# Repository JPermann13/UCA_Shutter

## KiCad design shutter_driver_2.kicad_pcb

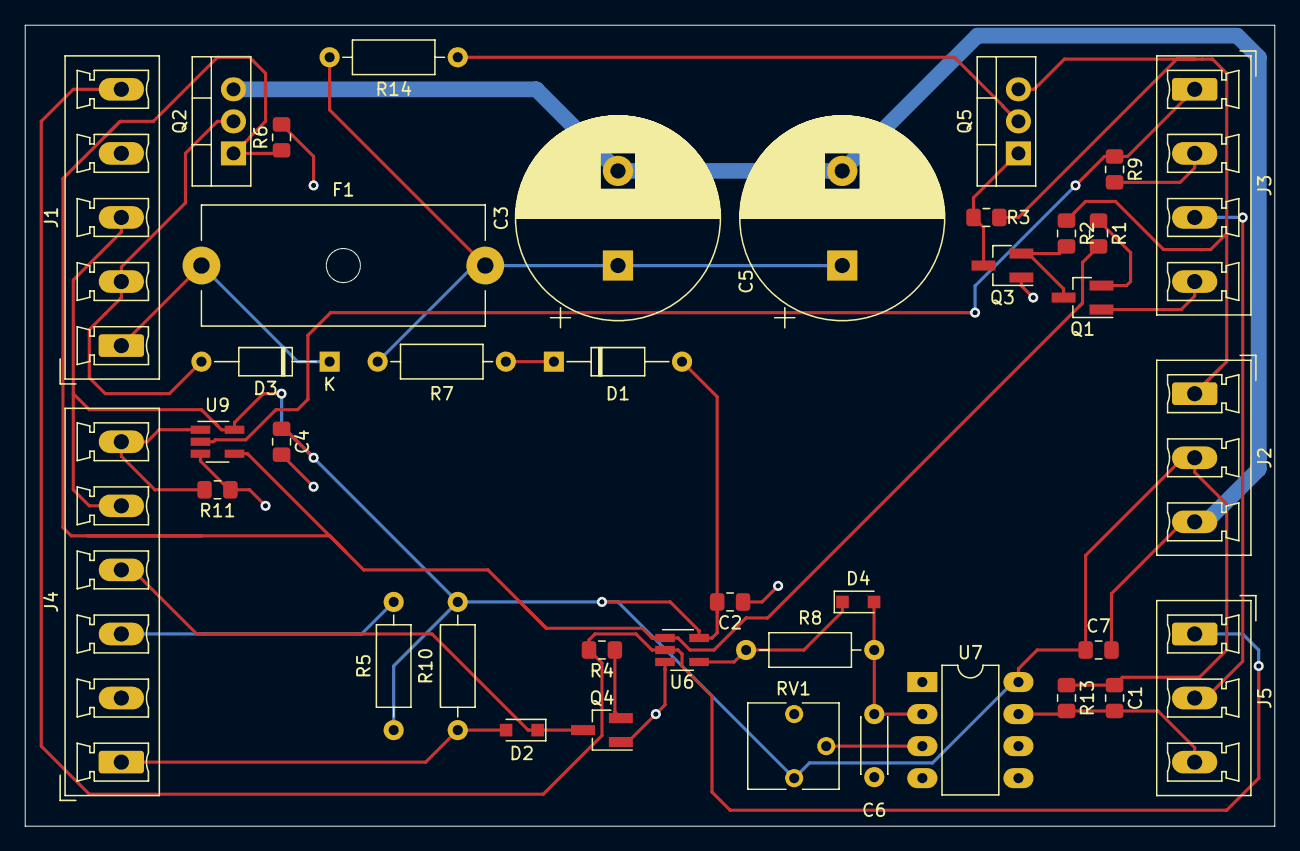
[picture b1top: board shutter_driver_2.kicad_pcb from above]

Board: 2 copper layers, 99.1 x 63.5 mm, 39 parts (0 on the bottom side), 24 nets.

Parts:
C1: 1n; C_0805_2012Metric_Pad1.15x1.40mm_HandSolder
C2, C4, C7: .1u; C_0805_2012Metric_Pad1.15x1.40mm_HandSolder
C3, C5: 2200u; CP_Radial_D16.0mm_P7.50mm
C6: 1u; C_Disc_D4.3mm_W1.9mm_P5.00mm
D1, D3: N4001; D_DO-35_SOD27_P10.16mm_Horizontal
D2, D4: 1N914; D_SOD-323_HandSoldering
F1: Fuse; Fuseholder_Cylinder-5x20mm_Schurter_0031_8201_Horizontal_Op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
J1: SHUTTER; PhoenixContact_MCV_1,5_5-G-5.08_1x05_P5.08mm_Vertical
J2: POWER; PhoenixContact_MCV_1,5_3-G-5.08_1x03_P5.08mm_Vertical
J3: I/O; PhoenixContact_MCV_1,5_4-G-5.08_1x04_P5.08mm_Vertical
J4: FRONT; PhoenixContact_MCV_1,5_6-G-5.08_1x06_P5.08mm_Vertical
J5: Switch; PhoenixContact_MCV_1,5_3-G-5.08_1x03_P5.08mm_Vertical
Q1, Q3, Q4: 2N3904; SOT-23_Handsoldering
Q2: FQP20N06L-ND; TO-220-3_Vertical
Q5: FQP17P06; TO-220-3_Vertical
R1, R2, R3, R6, R9, R11: 10K; R_0805_2012Metric_Pad1.15x1.40mm_HandSolder
R4: 4.7k; R_0805_2012Metric_Pad1.15x1.40mm_HandSolder
R5, R10: 220; R_Axial_DIN0207_L6.3mm_D2.5mm_P10.16mm_Horizontal
R7: 5; R_Axial_DIN0207_L6.3mm_D2.5mm_P10.16mm_Horizontal
R8: 50k; R_Axial_DIN0207_L6.3mm_D2.5mm_P10.16mm_Horizontal
R13: 10k; R_0805_2012Metric_Pad1.15x1.40mm_HandSolder
R14: 50; R_Axial_DIN0207_L6.3mm_D2.5mm_P10.16mm_Horizontal
RV1: 10k; Potentiometer_Vishay_T73YP_Vertical
U6, U9: SN74LVC1G86; SOT-23-5_HandSoldering
U7: LM311; DIP-8_W7.62mm_LongPads

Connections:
+5V: C1.1, C2.2, C4.1, C7.2, D1.2, J1.3, J2.2, J4.5, R5.1, R10.1, R13.1, RV1.1, U6.5, U7.8, U9.5
+24V: J2.1, Q5.3, R2.1, R3.1
/AMP_SIG: C1.2, J5.3, R13.2, U7.7
/CAP_POWER: C3.1, C5.1, F1.2, R7.2, R14.1
/LED_G+: D2.2, J4.1, R10.2
/LED_R+: J4.3, R5.2
/LED_R-: D2.1, J4.4, Q4.3
/OUT_TO_COMP: J3.3, J5.2
/SHUTTER_HIGH: D3.1, F1.1, J1.1
/SHUTTER_LOW: D3.2, J1.2, Q2.2
/SHUTTER_RET: J1.5, J5.1, R4.2, U6.2
/SIG: Q2.1, R1.2, R6.1, U6.1, U9.4
/SIG_IN: J3.1, R9.1, U9.2
GND: C2.1, C3.2, C4.2, C5.2, C6.2, C7.1, J1.4, J2.3, J3.2, J3.4, J4.2, Q1.1, Q2.3, Q3.1, Q4.1, R6.2, R9.2, R11.1, RV1.3, U6.3, U7.1, U7.4, U9.3
unnamed: C6.1, D4.2, R8.1, U7.2
unnamed: D1.1, R7.1
unnamed: D4.1, R8.2, U6.4
unnamed: J4.6, R11.2, U9.1
unnamed: Q1.2, R1.1
unnamed: Q1.3, Q3.2, R2.2
unnamed: Q3.3, Q5.1, R3.2
unnamed: Q4.2, R4.1
unnamed: Q5.2, R14.2
unnamed: RV1.2, U7.3
